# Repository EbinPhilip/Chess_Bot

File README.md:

# Chess_Bot #
Chess Playing Robot based on Arduino, Python, OpenCV and Stockfish Chess Engine 
## Requirements:
#### For Windows:
* Python 2.7
* Opencv 2.4
* python-chess: `pip install python-chess`
* imutils: `pip install imutils`
#### For Linux:
* All of the above^^ plus Stockfish 7 binaries(https://stockfishchess.org/download/)

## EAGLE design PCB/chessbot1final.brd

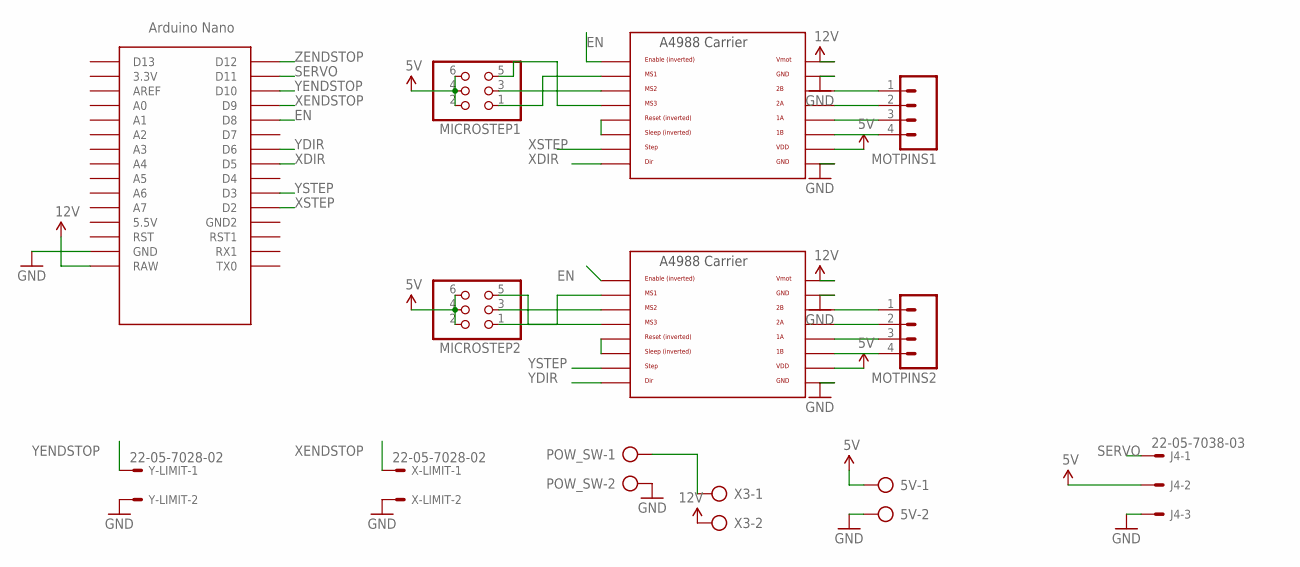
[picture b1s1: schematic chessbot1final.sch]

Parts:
5V: AK500/2
J4: 22-05-7038-03; 7395-03
MICROSTEP1, MICROSTEP2: PINHD-2X3; 2X03
MOTPINS1, MOTPINS2: M04PTH; 1X04
POW_SW: AK500/2
U$1, U$2: A4988BREAKOUT
U$3: NANO
X3: AK500/2
X-LIMIT: 22-05-7028-02; 7395-02
Y-LIMIT: 22-05-7028-02; 7395-02

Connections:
5V: 5V.1, J4.2, MICROSTEP1.2, MICROSTEP1.4, MICROSTEP1.6, MICROSTEP2.2, MICROSTEP2.4, MICROSTEP2.6, U$1.VDD, U$2.VDD
12V: U$1.VMOT, U$2.VMOT, U$3.RAW, X3.2
EN: U$1.EN, U$2.EN, U$3.D8
GND: 5V.2, J4.3, POW_SW.2, U$1.GND, U$1.GND@0 (GND), U$2.GND, U$2.GND@0 (GND), U$3.GND, X-LIMIT.2, Y-LIMIT.2
unnamed: MOTPINS1.4, U$2.1B
unnamed: MOTPINS1.3, U$2.1A
unnamed: MOTPINS1.2, U$2.2A
unnamed: MOTPINS1.1, U$2.2B
unnamed: MOTPINS2.1, U$1.2B
unnamed: MOTPINS2.2, U$1.2A
unnamed: MOTPINS2.3, U$1.1A
unnamed: MOTPINS2.4, U$1.1B
unnamed: MICROSTEP1.1, U$2.MS1
unnamed: MICROSTEP1.3, U$2.MS2
unnamed: U$2.RST, U$2.SLP (SLEEP)
unnamed: MICROSTEP2.3, U$1.MS2
unnamed: MICROSTEP2.1, U$1.MS1
unnamed: MICROSTEP2.5, U$1.MS3
unnamed: POW_SW.1, X3.1
unnamed: MICROSTEP1.5, U$2.MS3
unnamed: U$1.RST, U$1.SLP (SLEEP)
SERVO: J4.1, U$3.D11
XDIR: U$2.DIR, U$3.D5
XENDSTOP: U$3.D9, X-LIMIT.1
XSTEP: U$2.STEP, U$3.D2
YDIR: U$1.DIR, U$3.D6
YENDSTOP: U$3.D10, Y-LIMIT.1
YSTEP: U$1.STEP, U$3.D3
ZENDSTOP: U$3.D12

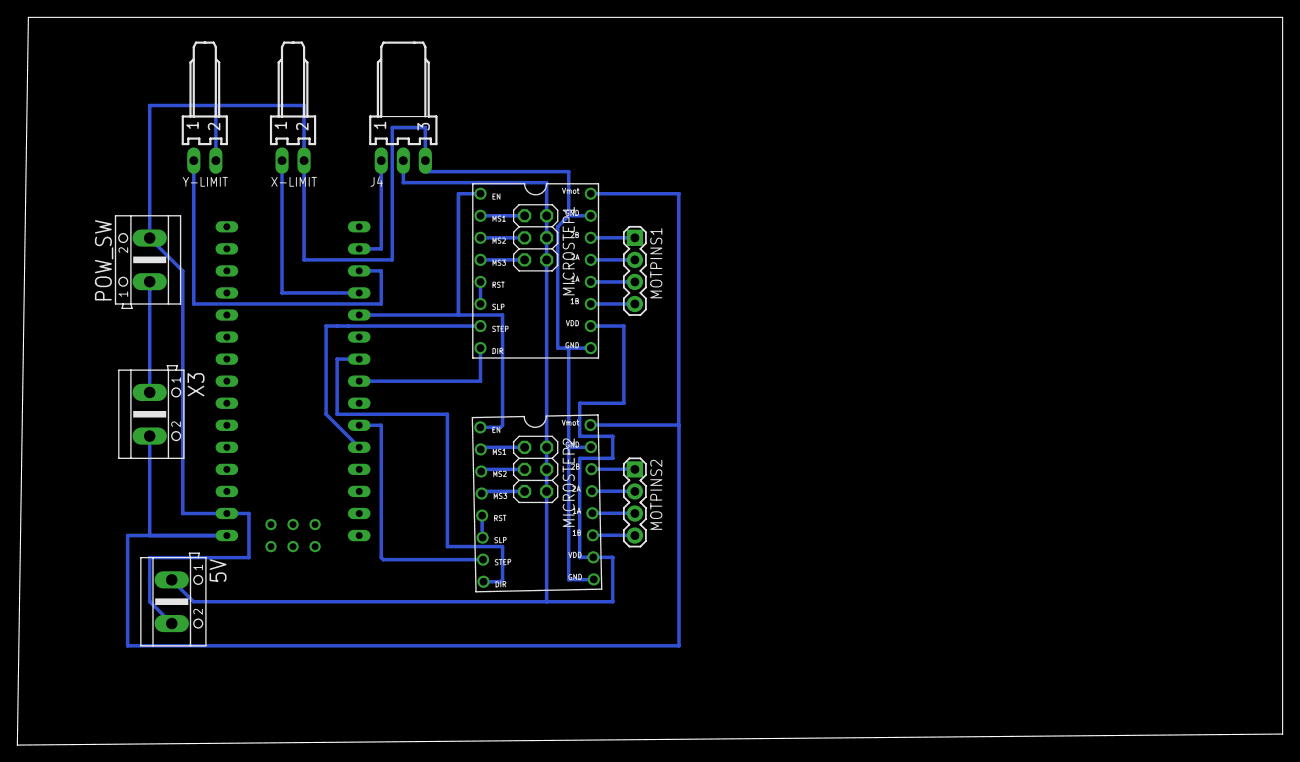
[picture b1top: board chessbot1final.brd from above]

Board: 2 copper layers, 145.7 x 83.8 mm, 13 parts (0 on the bottom side), 28 nets.

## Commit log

2018-02-11 First commit: complete opencv code
2018-02-11 added comments to main.py

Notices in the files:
parts and their libraries:
SparkFun-Connectors: Licensing: Creative Commons ShareAlike 4.0 International - https://creativecommons.org/licenses/by-sa/4.0
